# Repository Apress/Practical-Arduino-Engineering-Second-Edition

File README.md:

# Apress Source Code

This repository accompanies [*Practical Arduino Engineering, Second Edition*](https://link.springer.com/book/10.1007/978-1-4842-6852-0) by Harold Timmis (Apress, 2021).

[comment]: #cover

Download the files as a zip using the green button, or clone the repository to your machine using Git.

## Releases

Release v1.0 corresponds to the code in the published book, without corrections or updates.

## Contributions

See the file Contributing.md for more information on how you can contribute to this repository.

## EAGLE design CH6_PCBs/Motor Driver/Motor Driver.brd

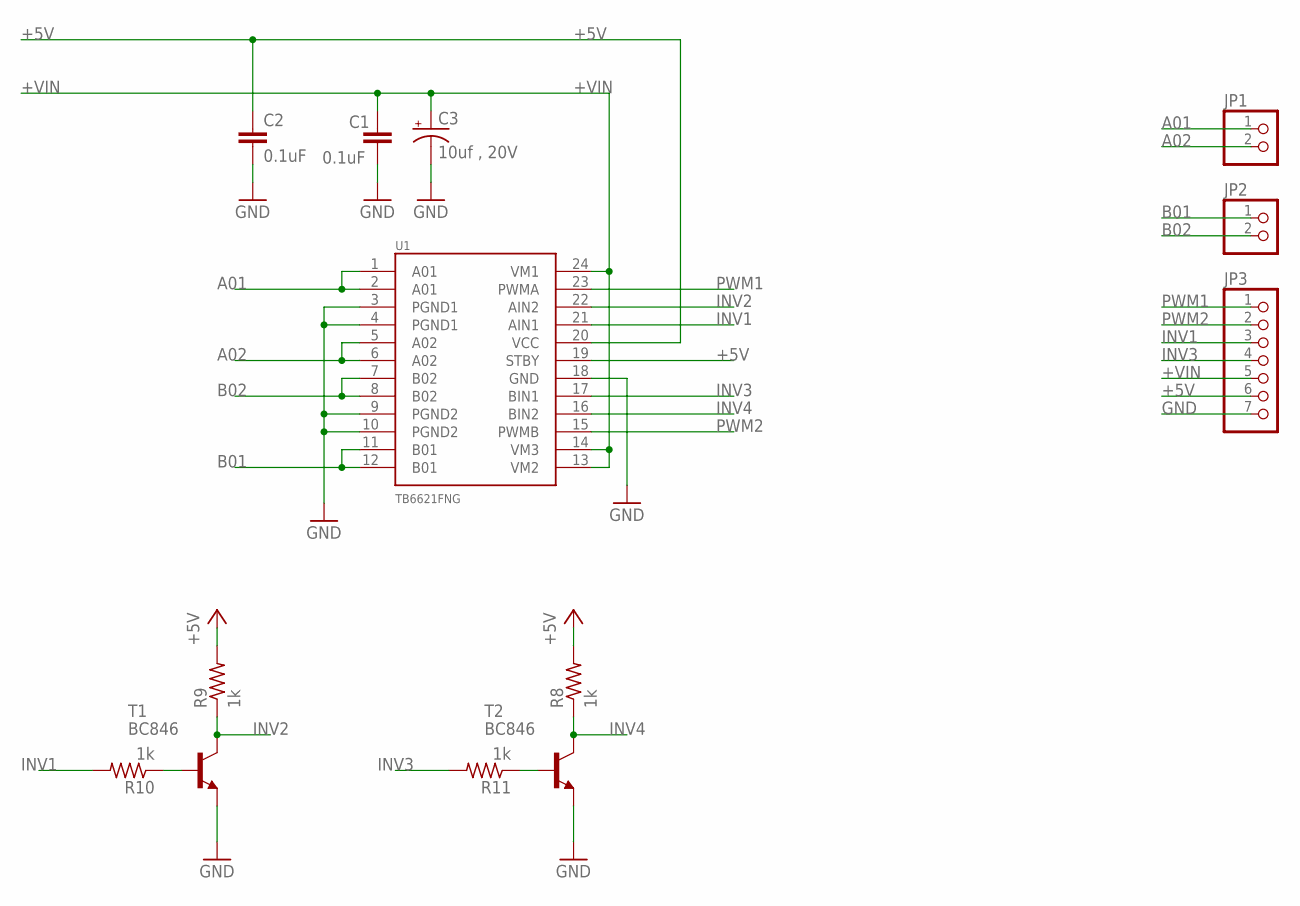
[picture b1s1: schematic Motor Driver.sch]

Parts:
C1, C2: 0.1uF; 0402-CAP
C3: 10uf , 20V; EIA3528
JP1, JP2: PINHD-1X2; 1X02
JP3: PINHD-1X7; 1X07
R8, R9, R10, R11: 1k; R0603
T1, T2: BC846; SOT23
U1: TB6621FNG; SSOP24

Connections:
+5V: C2.1, JP3.6, R8.2, R9.2, U1.19 (STBY), U1.20 (VCC)
+VIN: C1.1, C3.A (+), JP3.5, U1.13 (VM2), U1.14 (VM3), U1.24 (VM1)
A01: JP1.1, U1.1 (A01), U1.2 (A01)
A02: JP1.2, U1.5 (A02), U1.6 (A02)
B01: JP2.1, U1.11 (B01), U1.12 (B01)
B02: JP2.2, U1.7 (B02), U1.8 (B02)
GND: C1.2, C2.2, C3.C (-), JP3.7, T1.2 (E), T2.2 (E), U1.3 (PGND1), U1.4 (PGND1), U1.9 (PGND2), U1.10 (PGND2), U1.18 (GND)
INV1: JP3.3, R10.2, U1.21 (AIN1)
INV2: R9.1, T1.3 (C), U1.22 (AIN2)
INV3: JP3.4, R11.2, U1.17 (BIN1)
INV4: R8.1, T2.3 (C), U1.16 (BIN2)
unnamed: R10.1, T1.1 (B)
unnamed: R11.1, T2.1 (B)
PWM1: JP3.1, U1.23 (PWMA)
PWM2: JP3.2, U1.15 (PWMB)

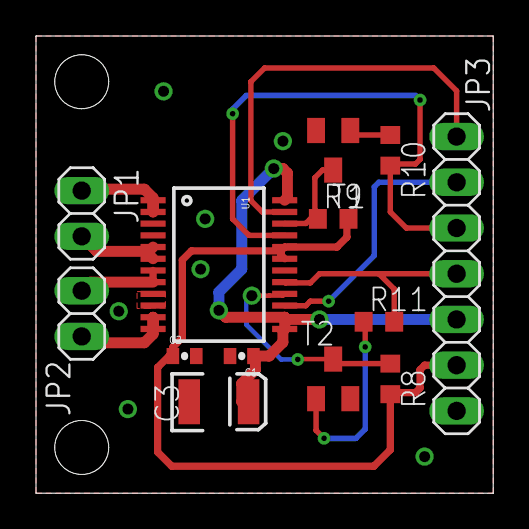
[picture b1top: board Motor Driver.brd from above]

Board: 2 copper layers, 25.4 x 25.4 mm, 13 parts (0 on the bottom side), 15 nets.

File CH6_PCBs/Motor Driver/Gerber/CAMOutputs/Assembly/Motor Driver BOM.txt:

Partlist exported from C:/Users/Pc/OneDrive - NA/Desktop/Desktop All FIles/Eagle Files/driver with TB6621FNG/Motor Driver.sch at 4/17/2020 10:00 PM

Qty Value       Device      Package  Parts            Description                     Found
2   0.1uF       CAP0402-CAP 0402-CAP C1, C2           Capacitor                       SparkFun-Capacitors -> Caps 
1   10uf , 20V  CAP_POL3528 EIA3528  C3               Capacitor Polarized             SparkFun-Capacitors -> 10UF-POLAR
4   1k          R-US_R0603  R0603    R8, R9, R10, R11 RESISTOR, American symbol       resistor -> R-US_
2   609-1317-ND PINHD-1X2   1X02     JP1, JP2         PIN HEADER                      pinhead -> PINHD-1X2
2   BC846       BC846       SOT23    T1, T2           NPN TRANSISTOR                  transistor -> BC846
1   TB6612FNG   TB6612FNG   SSOP24   U1               Toshiba 1A motor driver         SparkFun-IC-Special-Function -> TB6612FNG
1   WM4205-ND   PINHD-1X7   1X07     JP3              PIN HEADER                      pinhead -> PINHD-1X7

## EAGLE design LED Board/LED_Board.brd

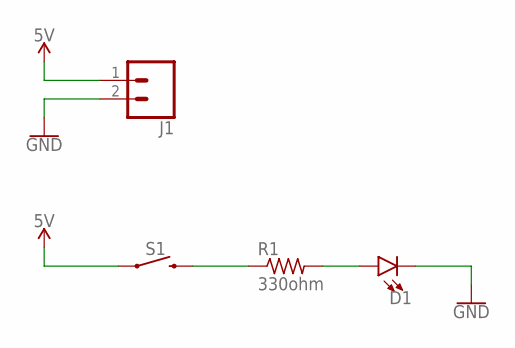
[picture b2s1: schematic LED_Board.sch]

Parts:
D1: LED3MM; LED_3MM
J1: CONN_025MM; SCREWTERMINAL-5MM-2
R1: 330ohm; R0805
S1: MOMENTARY-SWITCH-SPST-SMD-4.5MM; TACTILE_SWITCH_SMD_4.5MM

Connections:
5V: J1.1, S1.2 (1), S1.3 (1)
GND: D1.K (C), J1.2
unnamed: R1.1, S1.1 (2), S1.4 (2)
unnamed: D1.A, R1.2

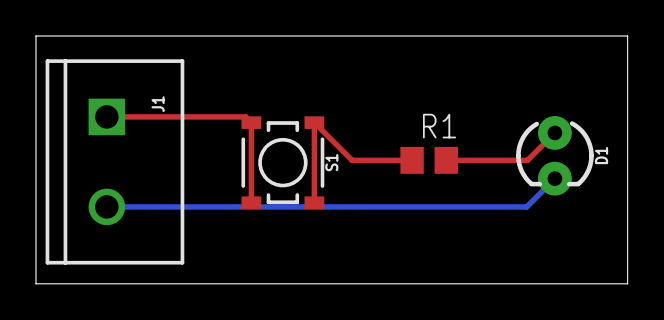
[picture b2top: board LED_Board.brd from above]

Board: 2 copper layers, 32.9 x 13.8 mm, 4 parts (0 on the bottom side), 4 nets.

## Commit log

2022-01-13 added source code

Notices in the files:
parts and their libraries:
SparkFun-LED: Licensing: Creative Commons ShareAlike 4.0 International - https://creativecommons.org/licenses/by-sa/4.0
